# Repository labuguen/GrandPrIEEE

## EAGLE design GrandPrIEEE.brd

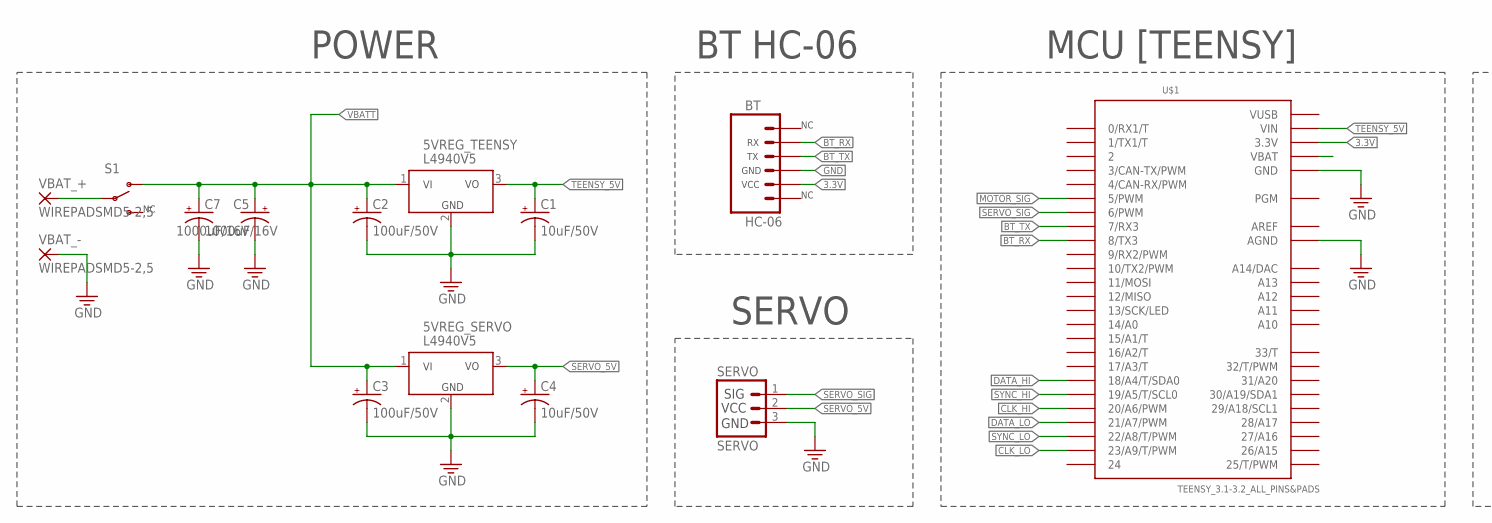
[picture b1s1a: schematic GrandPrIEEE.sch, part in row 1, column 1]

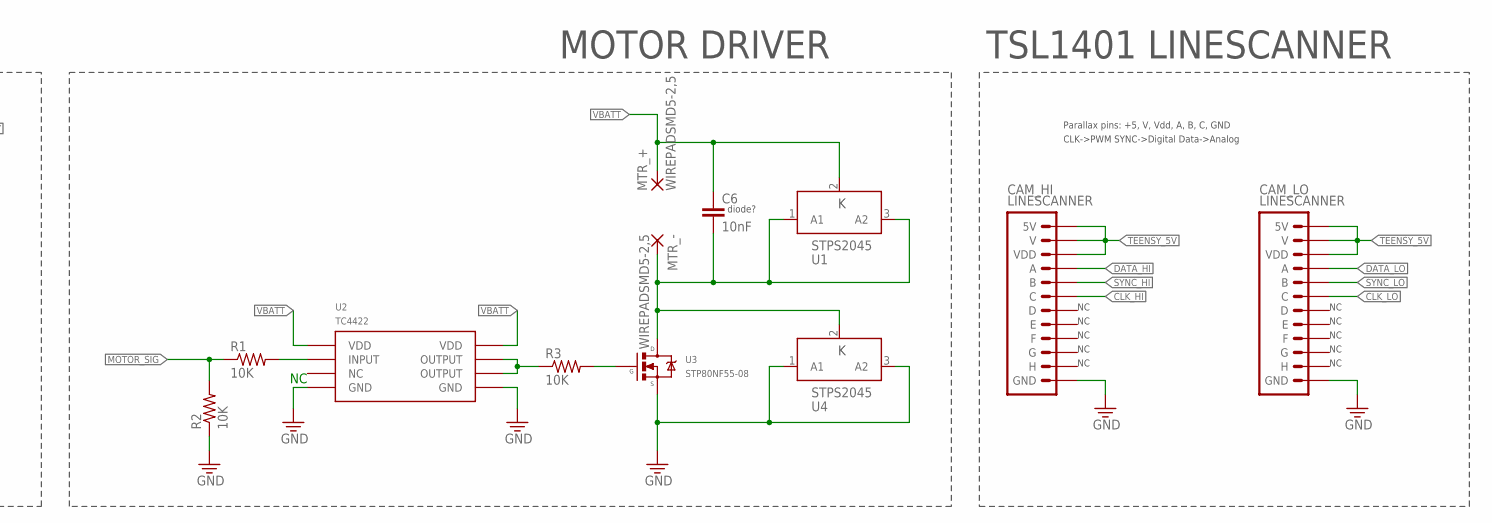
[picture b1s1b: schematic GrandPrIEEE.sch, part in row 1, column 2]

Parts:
5VREG_SERVO, 5VREG_TEENSY: L4940V5; TO-220-HEATSINK
BT: HC-06; 1X06
C1, C4: 10uF/50V; E2,5-5
C2, C3: 100uF/50V; E3,5-8
C5, C7: 1000uF/16V; E5-10,5
C6: 10nF; C025-025X050
CAM_HI: LINESCANNER
CAM_LO: LINESCANNER
MTR_+: WIREPADSMD5-2,5; 5-2,5
MTR_-: WIREPADSMD5-2,5; 5-2,5
R1, R2, R3: 10K; 0207/7
S1: SW_MTS-102C4; MTS-102C4
SERVO: SERVO; 1X03
U1, U4: STPS2045; TO-220
U2: TC4422; DIP-8
U3: STP80NF55-08; TO-220
U$1: TEENSY_3.1-3.2_ALL_PINS&PADS; TEENSY_3.0-3.2_ALL_PINS_&_PADS
VBAT_+: WIREPADSMD5-2,5; 5-2,5
VBAT_-: WIREPADSMD5-2,5; 5-2,5

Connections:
3.3V: BT.5 (VCC), U$1.3.3V, U$1.3.3V1 (3.3V), U$1.3.3V2 (3.3V)
AREF: U$1.AREF
BT_RX: BT.2 (RX), U$1.8 (8/TX3)
BT_TX: BT.3 (TX), U$1.7 (7/RX3)
CLK_HI: CAM_HI.6 (C), U$1.20/A6 (20/A6/PWM)
CLK_LO: CAM_LO.6 (C), U$1.23/A9 (23/A9/T/PWM)
DATA_HI: CAM_HI.4 (A), U$1.18/A4 (18/A4/T/SDA0)
DATA_LO: CAM_LO.4 (A), U$1.21/A7 (21/A7/PWM)
GND: 5VREG_SERVO.2 (GND), 5VREG_TEENSY.2 (GND), BT.4 (GND), C1.-, C2.-, C3.-, C4.-, C5.-, C7.-, CAM_HI.12 (GND), CAM_LO.12 (GND), R2.1, SERVO.3 (GND), U2.4 (GND), U2.5 (GND), U3.3 (S), U4.1 (A1), U4.3 (A2), U$1.AGND, U$1.GND, U$1.GND1 (GND), U$1.GND2 (GND), VBAT_-.1
MOTOR_SIG: R1.1, R2.2, U$1.5 (5/PWM)
unnamed: S1.P, VBAT_+.1
unnamed: R3.1, U2.6 (OUTPUT), U2.7 (OUTPUT)
unnamed: R1.2, U2.2 (INPUT)
unnamed: R3.2, U3.1 (G)
unnamed: C6.2, MTR_-.1, U1.1 (A1), U1.3 (A2), U3.2 (D), U4.2 (K)
SERVO_5V: 5VREG_SERVO.3 (VO), C4.+, SERVO.2 (VCC)
SERVO_SIG: SERVO.1 (SIG), U$1.6 (6/PWM)
SYNC_HI: CAM_HI.5 (B), U$1.19/A5 (19/A5/T/SCL0)
SYNC_LO: CAM_LO.5 (B), U$1.22/A8 (22/A8/T/PWM)
TEENSY_5V: 5VREG_TEENSY.3 (VO), C1.+, CAM_HI.1 (5V), CAM_HI.2 (V), CAM_HI.3 (VDD), CAM_LO.1 (5V), CAM_LO.2 (V), CAM_LO.3 (VDD), U$1.VIN
VBATT: 5VREG_SERVO.1 (VI), 5VREG_TEENSY.1 (VI), C2.+, C3.+, C5.+, C6.1, C7.+, MTR_+.1, S1.T2, U1.2 (K), U2.1 (VDD), U2.8 (VDD)
VUSB: U$1.VUSB

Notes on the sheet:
BT HC-06
MOTOR DRIVER
POWER
TSL1401 LINESCANNER
SERVO
diode?
Parallax pins: +5, V, Vdd, A, B, C, GND
CLK->PWM SYNC->Digital Data->Analog
MCU [TEENSY]

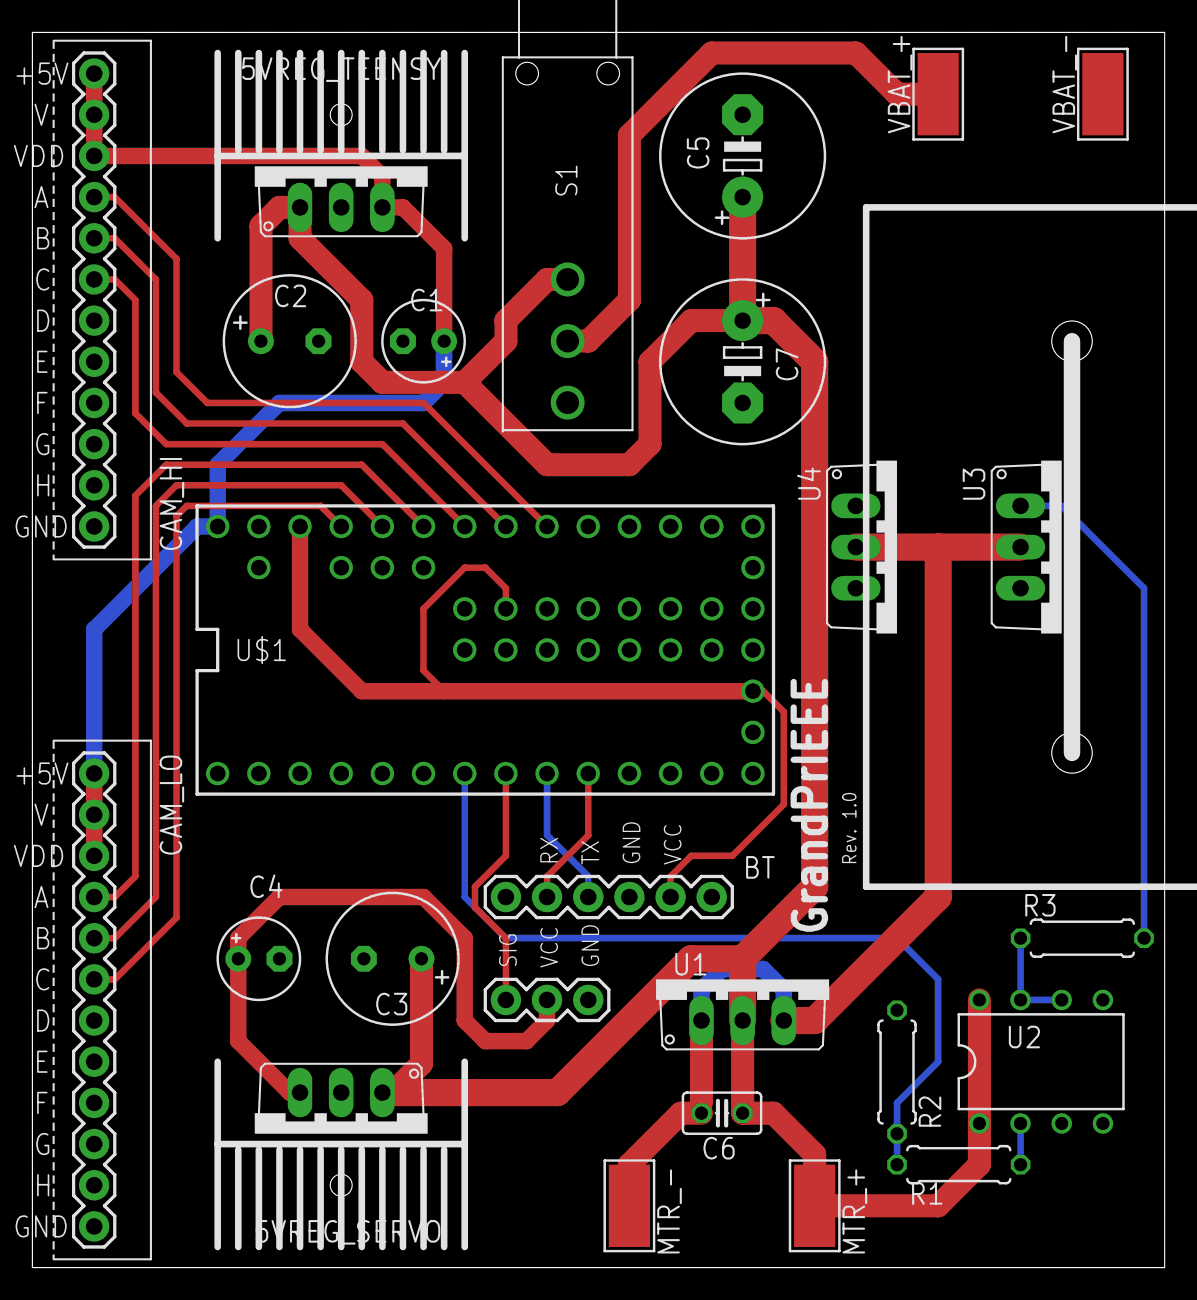
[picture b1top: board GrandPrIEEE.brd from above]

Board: 2 copper layers, 69.9 x 76.2 mm, 26 parts (0 on the bottom side), 20 nets.

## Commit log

2017-04-23 Finished GP board. Sent this version to fab
